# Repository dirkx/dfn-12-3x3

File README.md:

# dfn-12-3x3

DFN12 3x3mm adaptor board to 6x DIL/DIP for breadboards.

See https://aisler.net/dirkx/sandbox/tdfn12-3x3 for an an orderable version. Note that the alighnment of the tracks is not spot on (shifted 0.04mm up).

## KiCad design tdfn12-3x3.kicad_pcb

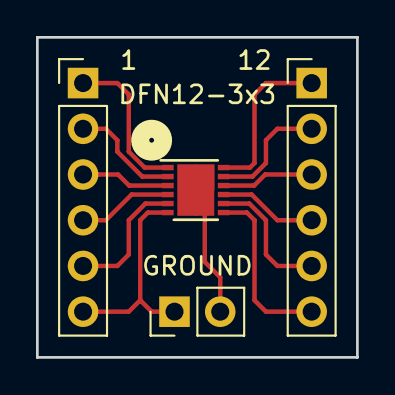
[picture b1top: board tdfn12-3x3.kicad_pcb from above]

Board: 2 copper layers, 17.8 x 17.8 mm, 4 parts (0 on the bottom side), 9 nets.

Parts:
1, 12: Conn_01x06; Pin_Header_Straight_1x06_Pitch2.54mm
DFN12-3x3: DS28S60; DFN-12-1EP_3x3mm_Pitch0.5mm
GROUND: Conn_01x02_Male; Pin_Header_Straight_1x02_Pitch2.54mm

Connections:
unnamed: 12.1, DFN12-3x3.12
unnamed: 12.6, DFN12-3x3.7
unnamed: 1.1, DFN12-3x3.1
unnamed: 1.2, DFN12-3x3.2
unnamed: 1.3, DFN12-3x3.3
unnamed: 1.4, DFN12-3x3.4
unnamed: 1.5, DFN12-3x3.5
unnamed: 1.6, DFN12-3x3.6, GROUND.1
unnamed: DFN12-3x3.13, GROUND.2

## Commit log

2020-10-13 version 3.00
2020-10-13 Add Aisler link. Remove .DS_Store
2020-10-13 Try to fix images links
2020-10-13 Fix other links too - apparently we cannot set the size.
